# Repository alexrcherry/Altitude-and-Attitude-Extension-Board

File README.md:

# Altitude-and-Attitude-Extension-Board
PCB design files for altitude and attitude extension board
## Purpose
The purpose of the Altitude and Attitude Extension Board is to measure the full state of a rocket. To do this, a gyroscope, accelerometer, gps, barometer and magnetometer are included on this board. A Kalman filter or some other means is necessary to get the full state of the rocket from the sensor data. The full state output of this board will be used to estimate the apogee of the rocket and to provide feedback for control systems.

| Requirement # | Requirement                                                                         | Justification                                                                                                                        | Testing Plan          |
| ------------- | ----------------------------------------------------------------------------------- | ------------------------------------------------------------------------------------------------------------------------------------ | --------------------- |
| R-001         | Shall fit in 4” diameter body tube                                                  | PCB needs to fit into L1 kits & Olympus expected diameter.                                                                           | Measure with calipers |
| R-002         | Will use 2x M2 or larger mounting bolts                                             | Needs to be mounted easily inside the avionics bay.                                                                                  | X                     |
| R-003         | Will use 5v input power supply                                                      | The main power bus running the length of the rocket is 5v.                                                                           | X                     |
| R-004         | Will draw less than 1A                                                              | The device should not greatly affect the power bus for other devices. Current is limited so that voltage sag is minimized.           | X                     |
| R-005         | Will have 2x CAN high connection                                                    | Needs two connections so the device can be daisy chained.                                                                            | X                     |
| R-006         | Will have 2x CAN low connections                                                    | Needs two connections so the device can be daisy chained.                                                                            | X                     |
| R-007         | Will have 2x Gnd connections                                                        | Needs two connections so the device can be daisy chained.                                                                            | X                     |
| R-008         | Will have 2x 5v+ connections                                                        | Needs two connections so the device can be daisy chained.                                                                            | X                     |
| R-009         | Will fulfill the requirements across the temperature range of -90 to 50 deg C       | Needs to work in the sun on the launch pad and in the cold upper atmosphere.                                                         | Real conditions, freezer, oven?        |
| R-010         | Will use CAN 2.0                                                                    | Communication needs to be compatible with all other boards, can 2.0 chosen for high speed.                                           | X                     |
| R-011         | Should use STM32 microcontroller                                                    | This requirement is somewhat flexible, stm32 is greatly preferred because that is what the club currently has experience with.       | X                     |
| R-012         | Should have greater than 1 deg heading accuracy over flight time                    | This information may be used for active control and needs to be as accurate as possible to minimize rocket dispersion.               |                       |
| R-013         | Should be able to measure 10 g or greater acceleration                              | Testing will be done on solid rockets which generally have greater acceleration.                                                     |                       |
| R-014         | Should be able to measure altitude within < 5% error to 130km                       | Needs to measure altitude for a spaceshot. This may end up being done with radio ranging instead of IMU integration.                 |                       |
| R-015         | Should be able to detect launch, apogee, and landing                                | Software needs to send a signal to the main processing board for these important flight events so that logging rate can be modified. |                       |

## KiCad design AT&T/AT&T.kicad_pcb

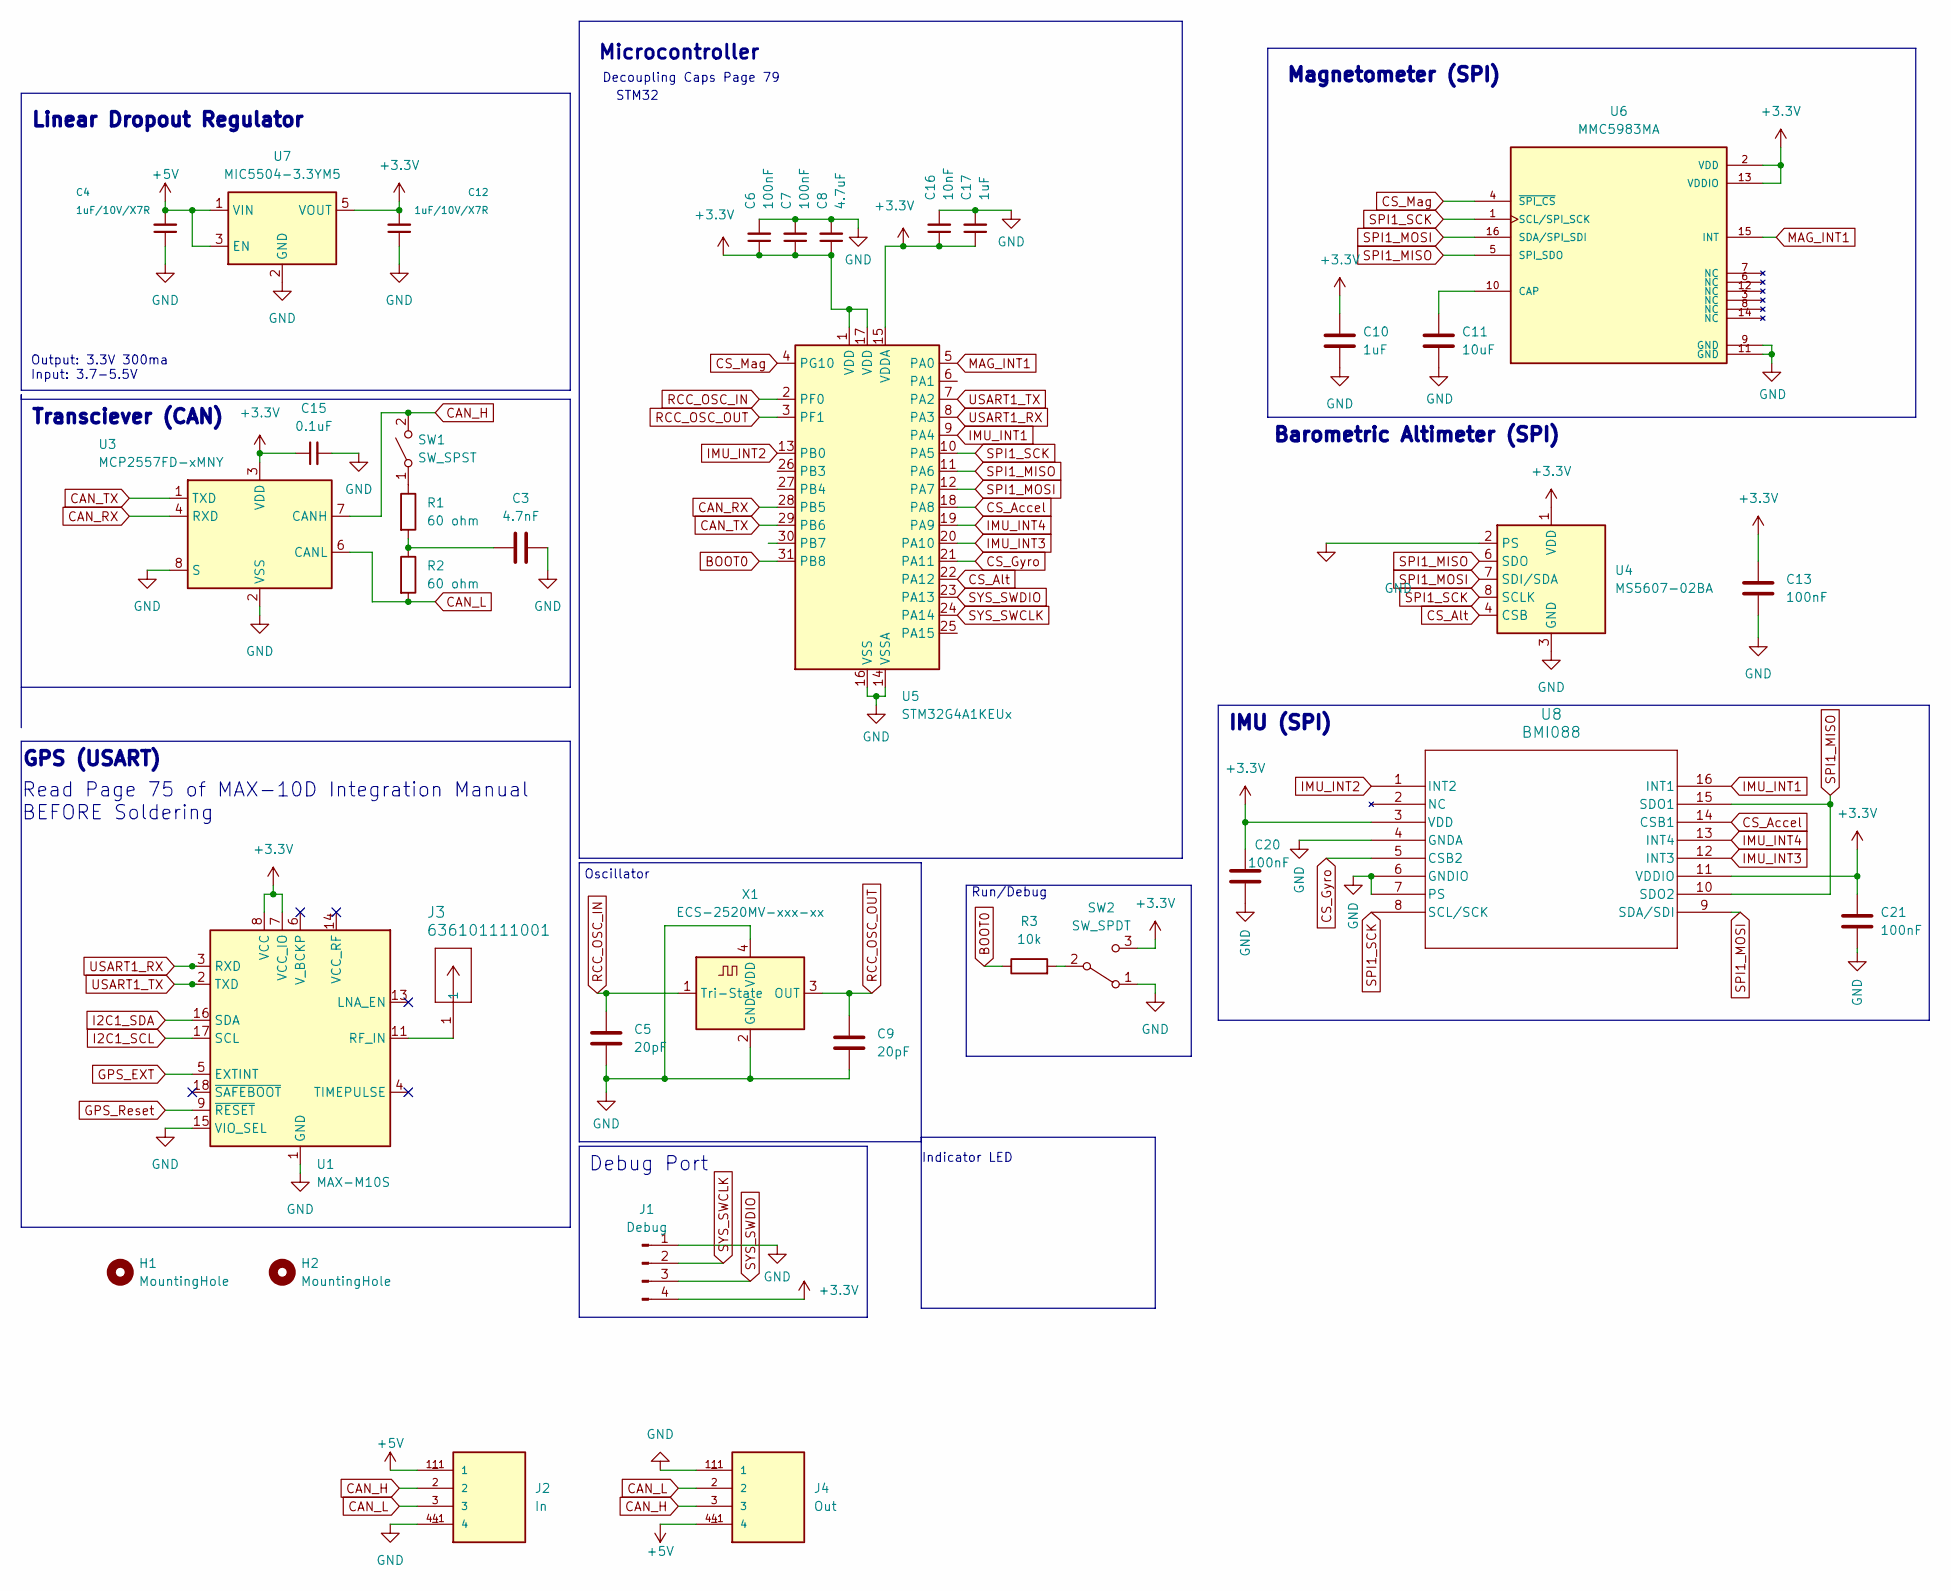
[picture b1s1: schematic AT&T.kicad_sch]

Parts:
C3: 4.7nF; C_0402_1005Metric
C4, C12: 1uF/10V/X7R; C_0603_1608Metric
C5, C9: 20pF; C_0402_1005Metric
C6, C7, C13, C20, C21: 100nF; C_0402_1005Metric
C8: 4.7uF; C_0402_1005Metric
C10, C17: 1uF; C_0402_1005Metric
C11: 10uF; C_0402_1005Metric
C15: 0.1uF; C_0402_1005Metric
C16: 10nF; C_0402_1005Metric
H1, H2: MountingHole; MountingHole_3.2mm_M3_DIN965_Pad_TopOnly
J1: Debug; PinHeader_1x04_P2.54mm_Vertical
J2: In; PHOENIX_1824543; PARTREV N/A; DigiKey_Part_Number 277-11572-2-ND
J3: 636101111001; CONN_636101111001_WRE
J4: Out; PHOENIX_1824543; PARTREV N/A; DigiKey_Part_Number 277-11572-2-ND
R1, R2: 60 ohm; R_0603_1608Metric
R3: 10k; R_0402_1005Metric
SW1: SW_SPST; SolderJumper-2_P1.3mm_Open_RoundedPad1.0x1.5mm
SW2: SW_SPDT; SolderJumper-3_P1.3mm_Open_RoundedPad1.0x1.5mm_NumberLabels
U1: MAX-M10S; ublox_MAX
U3: MCP2557FD-xMNY; TDFN-8-1EP_3x2mm_P0.5mm_EP1.80x1.65mm
U4: MS5607-02BA; LGA-8_3x5mm_P1.25mm
U5: STM32G4A1KEUx; QFN-32-1EP_5x5mm_P0.5mm_EP3.45x3.45mm
U6: MMC5983MA; MMC5983MA_MEM; PARTREV A
U7: MIC5504-3.3YM5; SOT-23-5
U8: BMI088; QFN_BMI085_BOS
X1: ECS-2520MV-xxx-xx; Oscillator_SMD_ECS_2520MV-xxx-xx-4Pin_2.5x2.0mm

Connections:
+3.3V: C6.1, C7.1, C8.1, C10.1, C12.2, C13.1, C15.1, C16.1, C17.1, C20.1, C21.1, J1.4, SW2.3 (C), U1.7 (VCC_IO), U1.8 (VCC), U3.3 (VDD), U4.1 (VDD), U5.1 (VDD), U5.15 (VDDA), U5.17 (VDD), U6.2 (VDD), U6.13 (VDDIO), U7.5 (VOUT), U8.3 (VDD), U8.11 (VDDIO); also elsewhere on the board
+5V: C4.2, J2.1, J2.1_1 (1), J4.4, J4.4_1 (4), U7.1 (VIN), U7.3 (EN)
BOOT0: R3.1, U5.31 (PB8)
CAN_H: J2.2, J4.3, SW1.2 (B), U3.7 (CANH); also elsewhere on the board
CAN_L: J2.3, J4.2, R2.2, U3.6 (CANL)
CAN_RX: U3.4 (RXD), U5.28 (PB5)
CAN_TX: U3.1 (TXD), U5.29 (PB6)
CS_Accel: U5.18 (PA8), U8.14 (CSB1)
CS_Alt: U4.4 (CSB), U4.5 (CSB), U5.22 (PA12)
CS_Gyro: U5.21 (PA11), U8.5 (CSB2)
CS_Mag: U5.4 (PG10), U6.4 (~SPI_CS)
GND: C3.2, C4.1, C5.2, C6.2, C7.2, C8.2, C9.2, C10.2, C11.2, C12.1, C13.2, C15.2, C16.2, C17.2, C20.2, C21.2, J1.1, J2.4, J2.4_1 (4), J4.1, J4.1_1 (1), SW2.1 (A), U1.1 (GND), U1.10 (GND), U1.12 (GND), U1.15 (VIO_SEL), U3.2 (VSS), U3.8 (S), U3.9 (VSS), U4.2 (PS), U4.3 (GND), U5.14 (VSSA), U5.16 (VSS), U5.32 (VSS), U5.33 (VSS), U6.9 (GND), U6.11 (GND), U7.2 (GND), U8.4 (GNDA), U8.6 (GNDIO), U8.7 (PS), X1.2 (GND), X1.4 (VDD); also elsewhere on the board
GPS_EXT: U1.5 (EXTINT)
GPS_Reset: U1.9 (~RESET)
I2C1_SCL: U1.17 (SCL)
I2C1_SDA: U1.16 (SDA)
IMU_INT1: U5.9 (PA4), U8.16 (INT1)
IMU_INT2: U5.13 (PB0), U8.1 (INT2)
IMU_INT3: U5.20 (PA10), U8.12 (INT3)
IMU_INT4: U5.19 (PA9), U8.13 (INT4)
MAG_INT1: U5.5 (PA0), U6.15 (INT)
unnamed: C3.1, R1.2, R2.1
unnamed 22: R1.1, SW1.1 (A); also elsewhere on the board
unnamed: R3.2, SW2.2 (B)
unnamed: J3.1, U1.11 (RF_IN)
unnamed: C11.1, U6.10 (CAP)
RCC_OSC_IN: C5.1, U5.2 (PF0), X1.1 (Tri-State)
RCC_OSC_OUT: C9.1, U5.3 (PF1), X1.3 (OUT)
SPI1_MISO: U4.6 (SDO), U5.11 (PA6), U6.5 (SPI_SDO), U8.10 (SDO2), U8.15 (SDO1)
SPI1_MOSI: U4.7 (SDI/SDA), U5.12 (PA7), U6.16 (SDA/SPI_SDI), U8.9 (SDA/SDI)
SPI1_SCK: U4.8 (SCLK), U5.10 (PA5), U6.1 (SCL/SPI_SCK), U8.8 (SCL/SCK)
SYS_SWCLK: J1.2, U5.24 (PA14); also elsewhere on the board
SYS_SWDIO: J1.3, U5.23 (PA13); also elsewhere on the board
USART1_RX: U1.3 (RXD), U5.8 (PA3)
USART1_TX: U1.2 (TXD), U5.7 (PA2)

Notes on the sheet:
Microcontroller
Output: 3.3V 300ma Input: 3.7-5.5V
Read Page 75 of MAX-10D Integration Manual BEFORE Soldering
Magnetometer (SPI)
Linear Dropout Regulator
Debug Port
Indicator LED
Decoupling Caps Page 79
Oscillator
Run/Debug
GPS (USART)
Transciever (CAN)
STM32
Barometric Altimeter (SPI)
IMU (SPI)

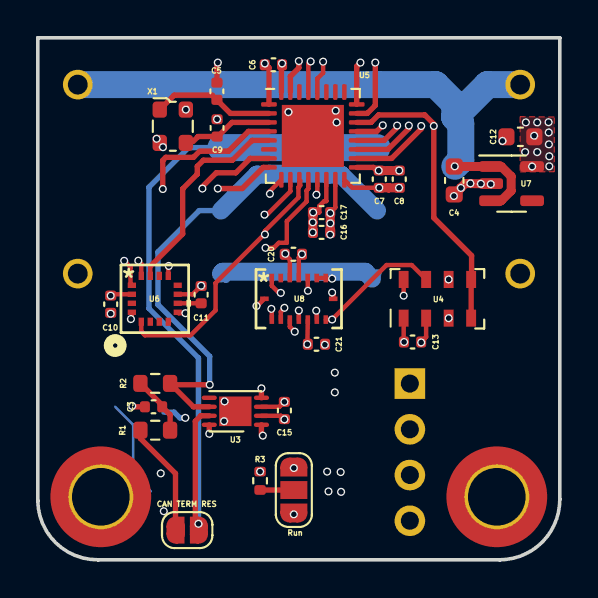
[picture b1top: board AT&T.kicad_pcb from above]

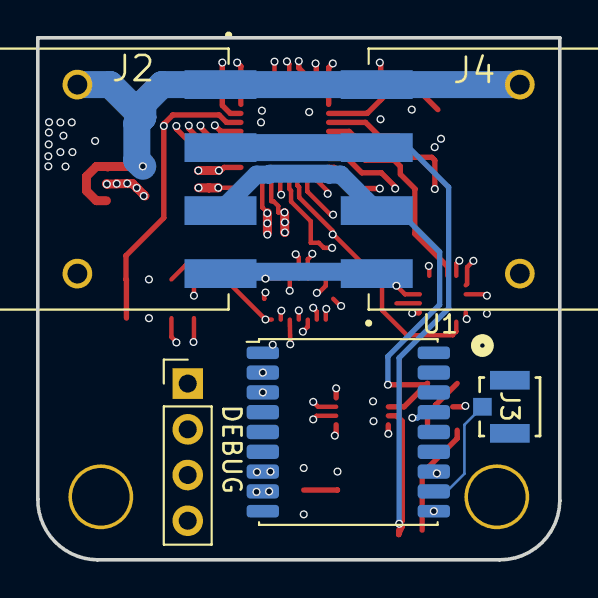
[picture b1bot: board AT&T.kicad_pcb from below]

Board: 6 copper layers, 29.0 x 29.0 mm, 35 parts (5 on the bottom side), 31 nets.

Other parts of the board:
CAN TERM RES: SW_SPST; SolderJumper-2_P1.3mm_Open_RoundedPad1.0x1.5mm
DEBUG: Debug; PinHeader_1x04_P2.54mm_Vertical

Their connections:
+3.3V: DEBUG.4; also elsewhere on the board
CAN_H: CAN TERM RES.2 (B); also elsewhere on the board
GND: DEBUG.1; also elsewhere on the board
unnamed 22: CAN TERM RES.1 (A); also elsewhere on the board
SYS_SWCLK: DEBUG.2; also elsewhere on the board
SYS_SWDIO: DEBUG.3; also elsewhere on the board

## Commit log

2023-09-05 V2 of the board
